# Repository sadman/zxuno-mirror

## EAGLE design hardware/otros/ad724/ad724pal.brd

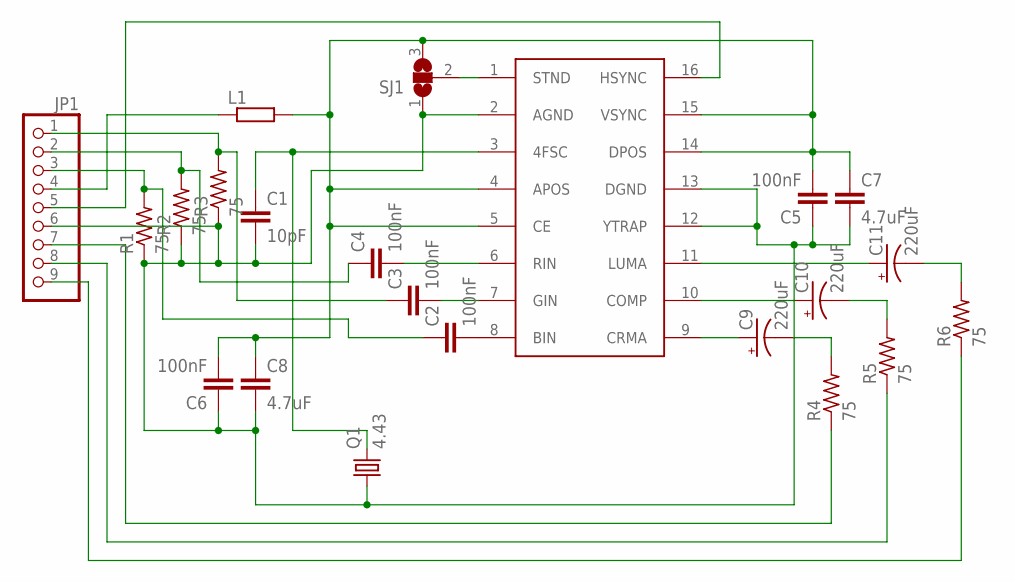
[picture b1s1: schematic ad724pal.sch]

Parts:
C1: 10pF; C0805
C2, C3, C4, C5, C6: 100nF; C0603
C7, C8: 4.7uF; C0805
C9, C10, C11: 220uF; E2,5-6
JP1: PINHD-1X9; 1X09
L1: R-EU_R0805; R0805
Q1: 4.43; HC49/S
R1, R2, R3, R4, R5, R6: 75; R0805
SJ1: SJ2W; SJ_2
U1: AD725; SO16W

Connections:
GND: C1.2, C5.1, C6.1, C7.2, C8.2, JP1.6, Q1.1, R1.1, R2.1, R3.1, SJ1.1, U1.2 (AGND), U1.12 (YTRAP), U1.13 (DGND)
unnamed: C4.1, JP1.2, R2.2
unnamed: SJ1.2, U1.1 (STND)
unnamed: C5.2, C6.2, C7.1, C8.1, L1.2, SJ1.3, U1.4 (APOS), U1.5 (CE), U1.14 (DPOS), U1.15 (VSYNC)
unnamed: C4.2, U1.6 (RIN)
unnamed: JP1.4, L1.1
unnamed: JP1.5, U1.16 (HSYNC)
unnamed: C3.2, U1.7 (GIN)
unnamed: C2.2, U1.8 (BIN)
unnamed: C3.1, JP1.1, R3.2
unnamed: C2.1, JP1.3, R1.2
unnamed: C1.1, Q1.2, U1.3 (4FSC)
unnamed: C11.+, U1.11 (LUMA)
unnamed: C10.+, U1.10 (COMP)
unnamed: C9.+, U1.9 (CRMA)
unnamed: C11.-, R6.2
unnamed: C10.-, R5.2
unnamed: C9.-, R4.2
unnamed: JP1.7, R4.1
unnamed: JP1.8, R5.1
unnamed: JP1.9, R6.1

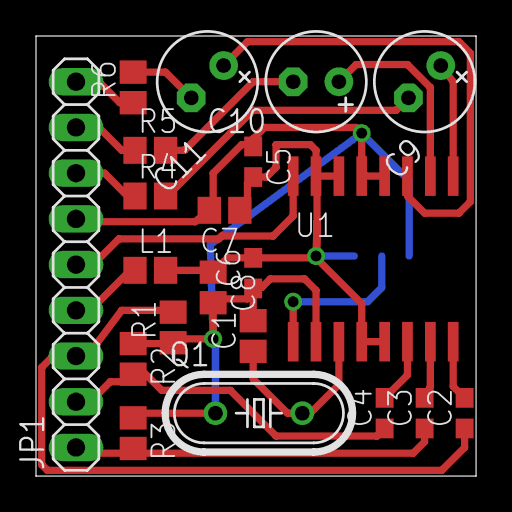
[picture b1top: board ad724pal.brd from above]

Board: 2 copper layers, 24.4 x 24.4 mm, 22 parts (1 on the bottom side), 21 nets.

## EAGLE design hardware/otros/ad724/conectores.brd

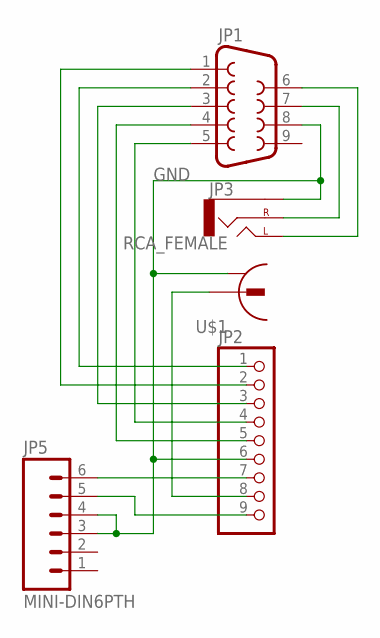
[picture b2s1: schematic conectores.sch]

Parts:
JP1: DB9MALE; DB9_MALE
JP2: PINHD-1X9; 1X09
JP3: AUDIO-JACKPTH; AUDIO-JACK
JP5: MINI-DIN6PTH; MINI-DIN6
U$1: RCA_FEMALE; RCA_EBAY

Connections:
GND: JP1.8, JP2.6, JP3.SLEEVE, JP5.3, JP5.4, U$1.1 (2)
unnamed: JP1.1, JP2.2
unnamed: JP1.2, JP2.1
unnamed: JP1.3, JP2.3
unnamed: JP1.4, JP2.5
unnamed: JP1.5, JP2.4
unnamed: JP1.6, JP3.TIP (LEFT)
unnamed: JP1.7, JP3.RING (RIGHT)
unnamed: JP2.9, JP5.5
unnamed: JP2.8, U$1.2 (1)
unnamed: JP2.7, JP5.6

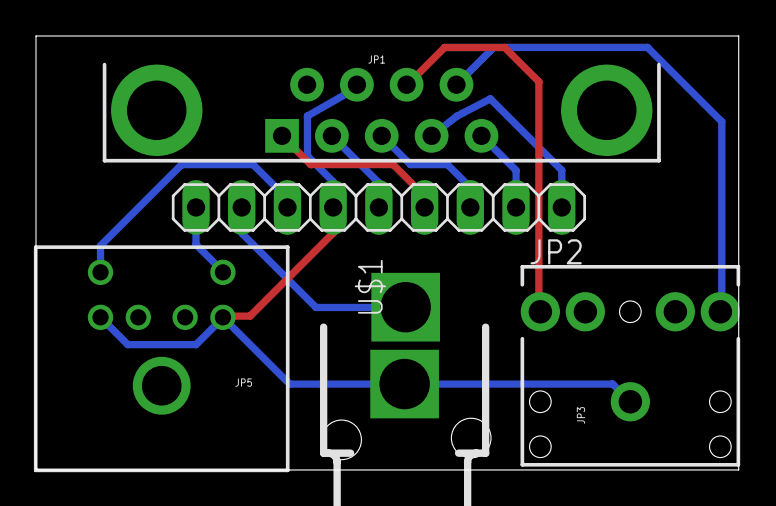
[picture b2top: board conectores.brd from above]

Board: 2 copper layers, 39.0 x 24.1 mm, 5 parts (0 on the bottom side), 11 nets.

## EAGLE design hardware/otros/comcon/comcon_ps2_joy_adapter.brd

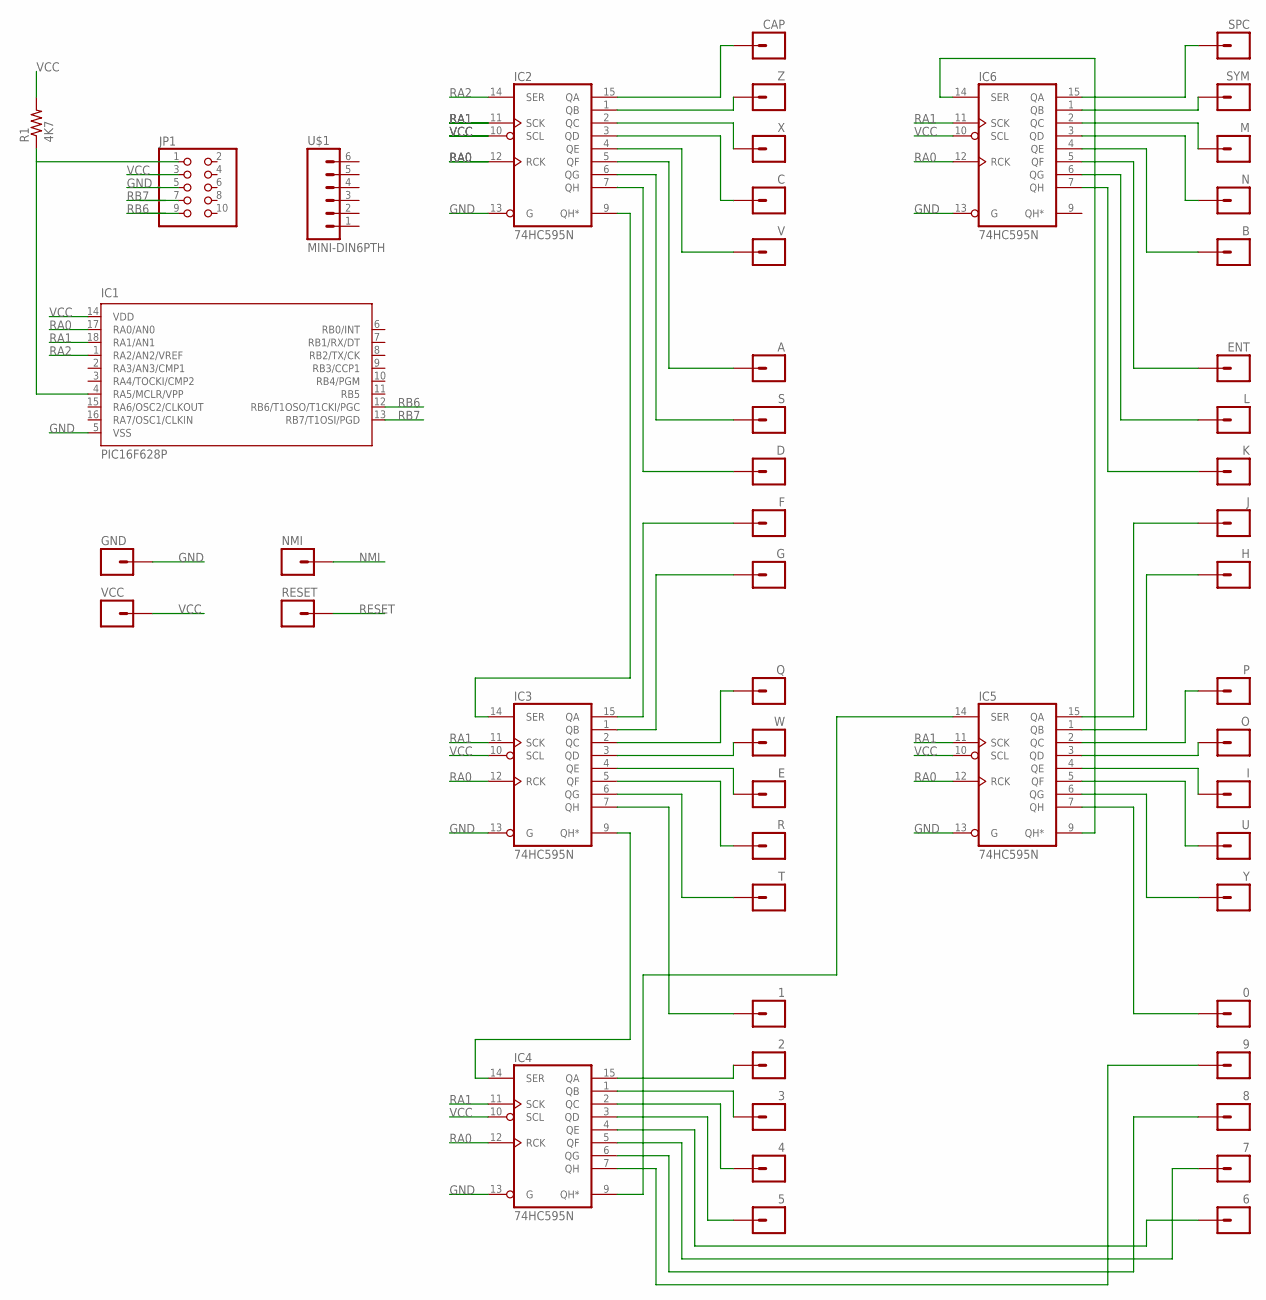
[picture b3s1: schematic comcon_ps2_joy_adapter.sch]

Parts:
0, 1, 2, 3, 4, 5, 6, 7, 8, 9: M01PTH; 1X01
A: M01PTH; 1X01
B: M01PTH; 1X01
C: M01PTH; 1X01
CAP: M01PTH; 1X01
D: M01PTH; 1X01
E: M01PTH; 1X01
ENT: M01PTH; 1X01
F: M01PTH; 1X01
G: M01PTH; 1X01
GND: M01PTH; 1X01
H: M01PTH; 1X01
I: M01PTH; 1X01
IC1: PIC16F628P; DIL18
IC2, IC3, IC4, IC5, IC6: 74HC595N; DIL16
J: M01PTH; 1X01
JP1: PINHD-2X5; 2X05
K: M01PTH; 1X01
L: M01PTH; 1X01
M: M01PTH; 1X01
N: M01PTH; 1X01
NMI: M01PTH; 1X01
O: M01PTH; 1X01
P: M01PTH; 1X01
Q: M01PTH; 1X01
R: M01PTH; 1X01
R1: 4K7; 0207/7
RESET: M01PTH; 1X01
S: M01PTH; 1X01
SPC: M01PTH; 1X01
SYM: M01PTH; 1X01
T: M01PTH; 1X01
U: M01PTH; 1X01
U$1: MINI-DIN6PTH; MINI-DIN6
V: M01PTH; 1X01
VCC: M01PTH; 1X01
W: M01PTH; 1X01
X: M01PTH; 1X01
Y: M01PTH; 1X01
Z: M01PTH; 1X01

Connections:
GND: GND.1, IC1.5 (VSS), IC2.8 (GND), IC2.13 (G), IC3.8 (GND), IC3.13 (G), IC4.8 (GND), IC4.13 (G), IC5.8 (GND), IC5.13 (G), IC6.8 (GND), IC6.13 (G), JP1.5
unnamed: A.1, IC2.5 (QF)
unnamed: IC2.6 (QG), S.1
unnamed: IC2.9 (QH*), IC3.14 (SER)
unnamed: IC5.9 (QH*), IC6.14 (SER)
unnamed: IC3.9 (QH*), IC4.14 (SER)
unnamed: IC4.9 (QH*), IC5.14 (SER)
unnamed: IC1.4 (RA5/MCLR/VPP), JP1.1, R1.1
unnamed: IC6.1 (QB), SYM.1
unnamed: IC6.2 (QC), M.1
unnamed: IC6.3 (QD), N.1
unnamed: B.1, IC6.4 (QE)
unnamed: CAP.1, IC2.15 (QA)
unnamed: IC2.1 (QB), Z.1
unnamed: IC2.2 (QC), X.1
unnamed: C.1, IC2.3 (QD)
unnamed: IC2.4 (QE), V.1
unnamed: ENT.1, IC6.5 (QF)
unnamed: IC6.6 (QG), L.1
unnamed: IC6.7 (QH), K.1
unnamed: IC5.15 (QA), J.1
unnamed: H.1, IC5.1 (QB)
unnamed: D.1, IC2.7 (QH)
unnamed: F.1, IC3.15 (QA)
unnamed: G.1, IC3.1 (QB)
unnamed: IC5.3 (QD), O.1
unnamed: I.1, IC5.4 (QE)
unnamed: IC5.5 (QF), U.1
unnamed: IC5.6 (QG), Y.1
unnamed: IC3.3 (QD), W.1
unnamed: E.1, IC3.4 (QE)
unnamed: IC3.5 (QF), R.1
unnamed: IC3.6 (QG), T.1
unnamed: 0.1, IC5.7 (QH)
unnamed: 9.1, IC4.7 (QH)
unnamed: 8.1, IC4.6 (QG)
unnamed: 7.1, IC4.5 (QF)
unnamed: 6.1, IC4.4 (QE)
unnamed: 1.1, IC3.7 (QH)
unnamed: 2.1, IC4.15 (QA)
unnamed: 3.1, IC4.1 (QB)
unnamed: 4.1, IC4.2 (QC)
unnamed: 5.1, IC4.3 (QD)
NMI: NMI.1
RA0: IC2.12 (RCK), IC3.12 (RCK), IC4.12 (RCK), IC5.12 (RCK), IC6.12 (RCK)
RA1: IC2.11 (SCK), IC3.11 (SCK), IC4.11 (SCK), IC5.11 (SCK), IC6.11 (SCK)
RA2: IC2.14 (SER)
RB6: IC1.12 (RB6/T1OSO/T1CKI/PGC)
RB7: IC1.13 (RB7/T1OSI/PGD)
RESET: RESET.1
VCC: IC2.10 (SCL), IC2.16 (VCC), IC3.10 (SCL), IC3.16 (VCC), IC4.10 (SCL), IC4.16 (VCC), IC5.10 (SCL), IC5.16 (VCC), IC6.10 (SCL), IC6.16 (VCC), JP1.3, R1.2, VCC.1
VDD: IC1.14 (VDD)

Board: 2 copper layers, 53 parts (0 on the bottom side), 46 nets, no tracks yet.

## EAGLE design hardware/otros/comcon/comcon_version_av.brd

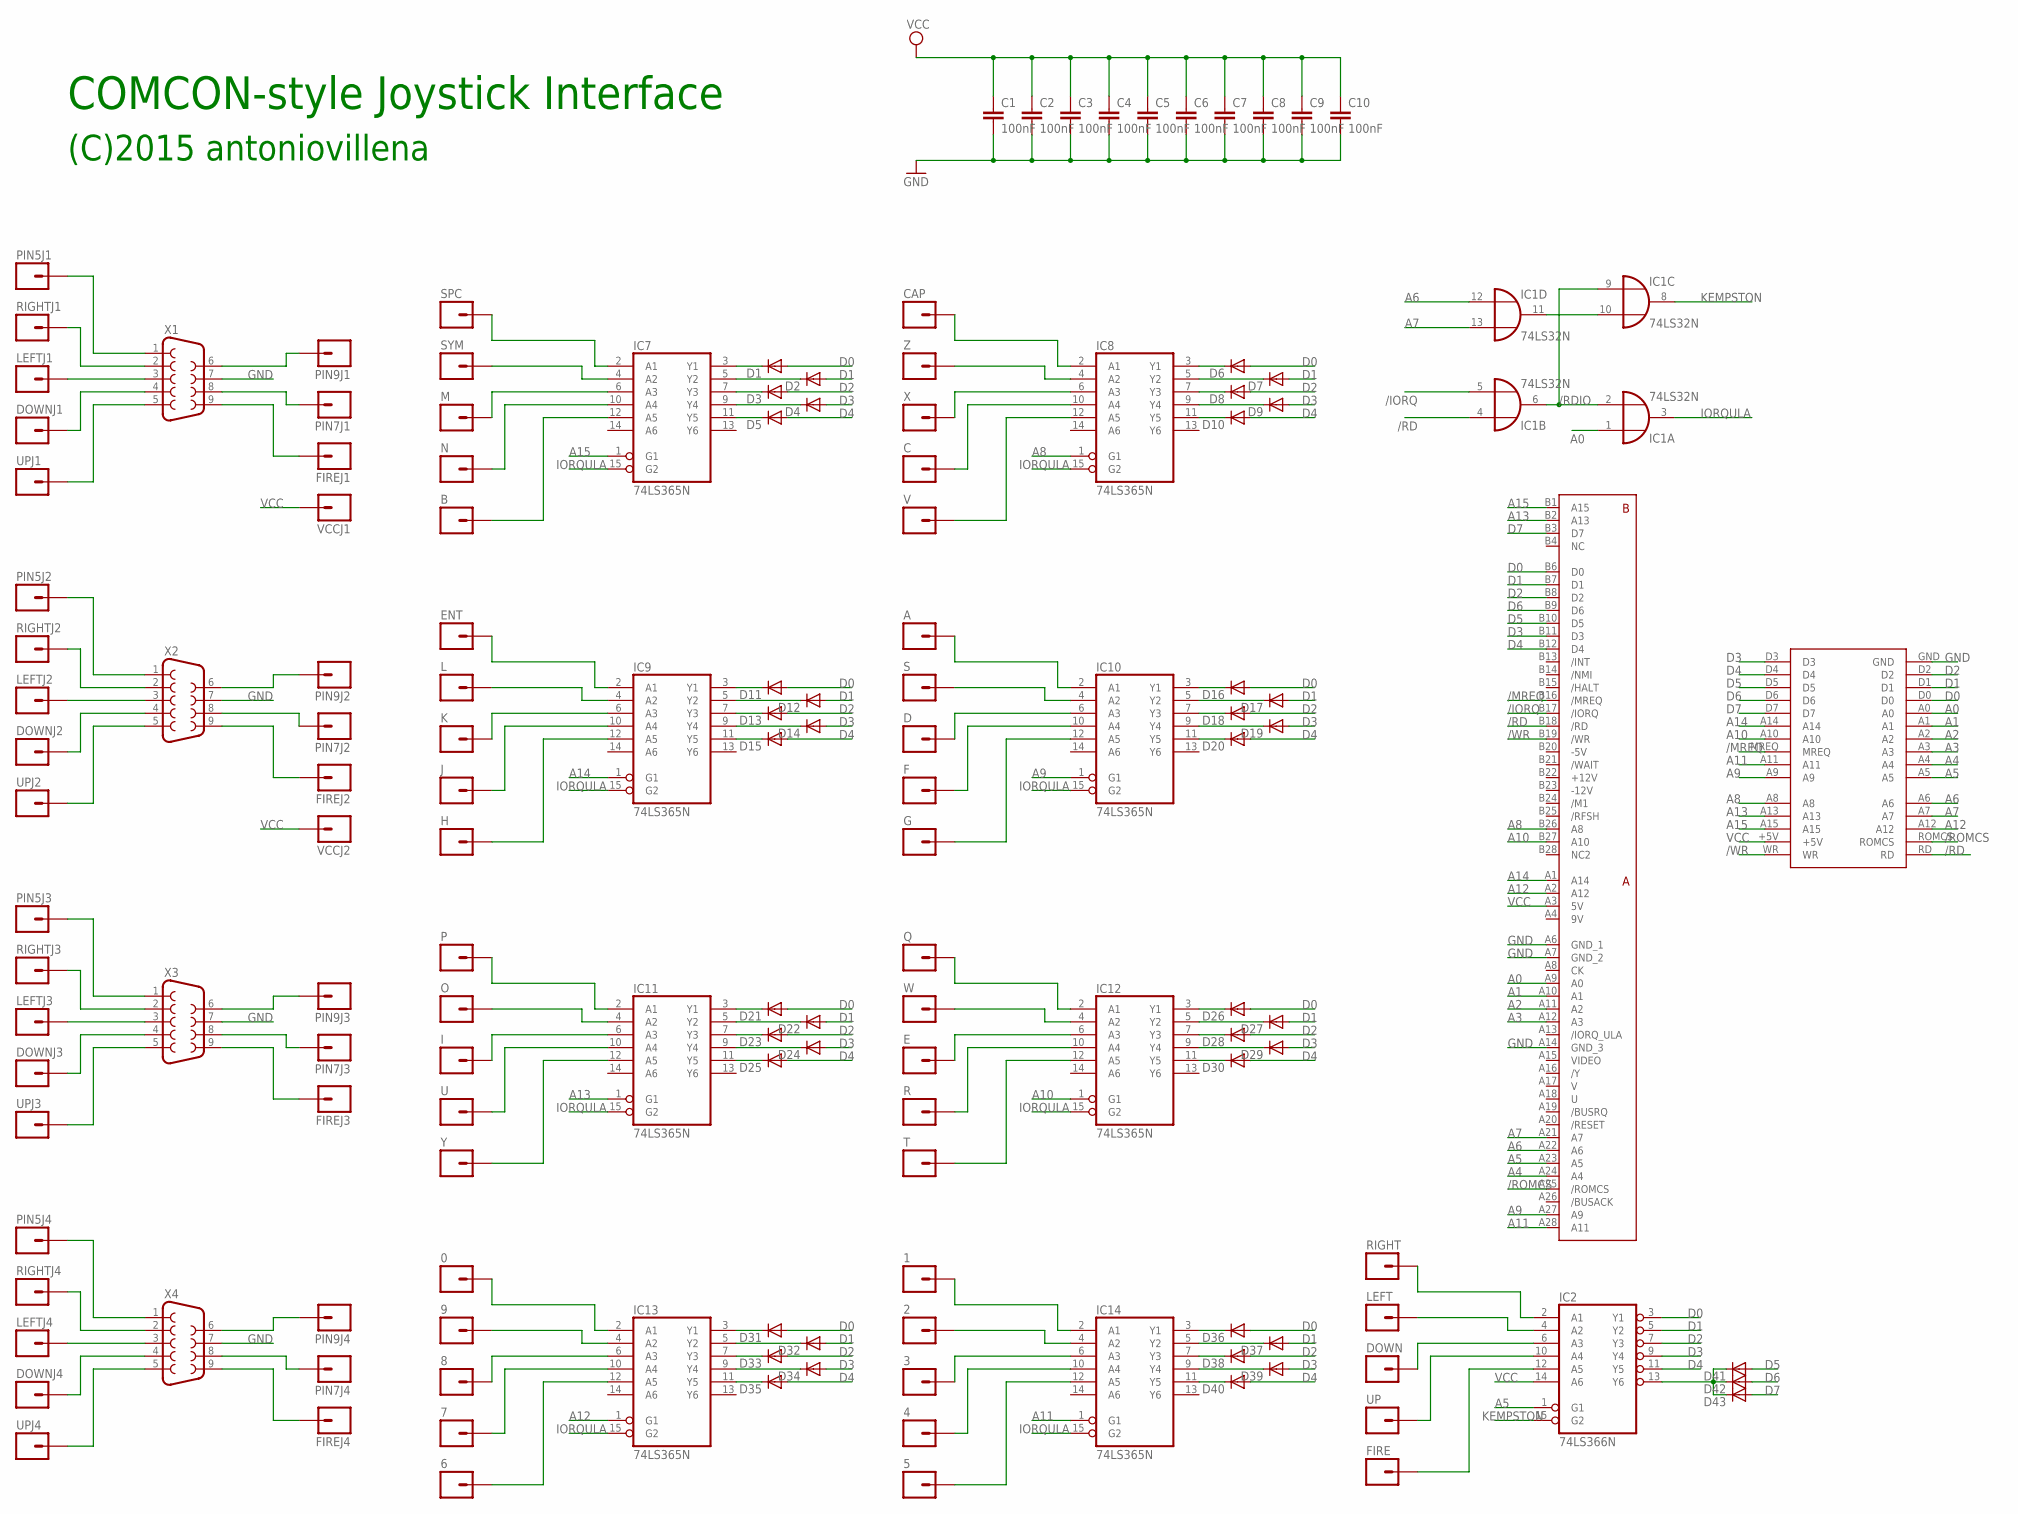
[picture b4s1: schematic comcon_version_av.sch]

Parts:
0, 1, 2, 3, 4, 5, 6, 7, 8, 9: M01PTH; 1X01
A: M01PTH; 1X01
B: M01PTH; 1X01
C: M01PTH; 1X01
C1, C2, C3, C4, C5, C6, C7, C8, C9, C10: 100nF; C050-025X075
CAP: M01PTH; 1X01
D: M01PTH; 1X01
D1, D2, D3, D4, D5, D6, D7, D8, D9, D10, D11, D12, D13, D14, D15, D16, D17, D18, D19, D20, D21, D22, D23, D24, D25, D26, D27, D28, D29, D30, D31, D32, D33, D34, D35, D36, D37, D38, D39, D40, D43: 1N4148DO35-7; DO35-7
D41, D42: 1N4148DO35-10; DO35-10
DOWN: M01PTH; 1X01
DOWNJ1, DOWNJ2, DOWNJ3, DOWNJ4: M01PTH; 1X01
E: M01PTH; 1X01
ENT: M01PTH; 1X01
F: M01PTH; 1X01
FIRE: M01PTH; 1X01
FIREJ1, FIREJ2, FIREJ3, FIREJ4: M01PTH; 1X01
G: M01PTH; 1X01
H: M01PTH; 1X01
I: M01PTH; 1X01
IC1: 74LS32N; DIL14
IC2: 74LS366N; DIL16
IC7, IC8, IC9, IC10, IC11, IC12, IC13, IC14: 74LS365N; DIL16
J: M01PTH; 1X01
K: M01PTH; 1X01
L: M01PTH; 1X01
LEFT: M01PTH; 1X01
LEFTJ1, LEFTJ2, LEFTJ3, LEFTJ4: M01PTH; 1X01
M: M01PTH; 1X01
N: M01PTH; 1X01
O: M01PTH; 1X01
P: M01PTH; 1X01
PIN5J1, PIN5J2, PIN5J3, PIN5J4, PIN7J1, PIN7J2, PIN7J3, PIN7J4, PIN9J1, PIN9J2, PIN9J3, PIN9J4: M01PTH; 1X01
Q: M01PTH; 1X01
R: M01PTH; 1X01
RIGHT: M01PTH; 1X01
RIGHTJ1, RIGHTJ2, RIGHTJ3, RIGHTJ4: M01PTH; 1X01
S: M01PTH; 1X01
SPC: M01PTH; 1X01
SYM: M01PTH; 1X01
T: M01PTH; 1X01
U: M01PTH; 1X01
U$1: ZX_CARTRIDGE
U$3: ZXSP_ED2X28_SPE; 2X28_SPE
UP: M01PTH; 1X01
UPJ1, UPJ2, UPJ3, UPJ4: M01PTH; 1X01
V: M01PTH; 1X01
VCCJ1, VCCJ2: M01PTH; 1X01
W: M01PTH; 1X01
X: M01PTH; 1X01
X1, X2, X3, X4: F09D
Y: M01PTH; 1X01
Z: M01PTH; 1X01

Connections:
9V: U$3.A4 (9V)
+12V: U$3.B22 (+12V)
-5V: U$3.B20 (-5V)
-12V: U$3.B23 (-12V)
/IORQ: IC1.5 (I1), U$3.B17 (/IORQ)
/MREQ: U$1.MREQ, U$3.B16 (/MREQ)
/RD: IC1.4 (I0), U$1.RD, U$3.B18 (/RD)
/RDIO: IC1.2 (I1), IC1.6 (O), IC1.9 (I0)
/ROMCS: U$1.ROMCS, U$3.A25 (/ROMCS)
/WR: U$1.WR, U$3.B19 (/WR)
A0: IC1.1 (I0), U$1.A0, U$3.A9 (A0)
A1: U$1.A1, U$3.A10 (A1)
A2: U$1.A2, U$3.A11 (A2)
A3: U$1.A3, U$3.A12 (A3)
A4: U$1.A4, U$3.A24 (A4)
A5: IC2.1 (G1), U$1.A5, U$3.A23 (A5)
A6: IC1.12 (I0), U$1.A6, U$3.A22 (A6)
A7: IC1.13 (I1), U$1.A7, U$3.A21 (A7)
A8: IC8.1 (G1), U$1.A8, U$3.B26 (A8)
A9: IC10.1 (G1), U$1.A9, U$3.A27 (A9)
A10: IC12.1 (G1), U$1.A10, U$3.B27 (A10)
A11: IC14.1 (G1), U$1.A11, U$3.A28 (A11)
A12: IC13.1 (G1), U$1.A12, U$3.A2 (A12)
A13: IC11.1 (G1), U$1.A13, U$3.B2 (A13)
A14: IC9.1 (G1), U$1.A14, U$3.A1 (A14)
A15: IC7.1 (G1), U$1.A15, U$3.B1 (A15)
D0: D1.A, D6.A, D11.A, D16.A, D21.A, D26.A, D31.A, D36.A, IC2.3 (Y1), U$1.D0, U$3.B6 (D0)
D1: D2.A, D7.A, D12.A, D17.A, D22.A, D27.A, D32.A, D37.A, IC2.5 (Y2), U$1.D1, U$3.B7 (D1)
D2: D3.A, D8.A, D13.A, D18.A, D23.A, D28.A, D33.A, D38.A, IC2.7 (Y3), U$1.D2, U$3.B8 (D2)
D3: D4.A, D9.A, D14.A, D19.A, D24.A, D29.A, D34.A, D39.A, IC2.9 (Y4), U$1.D3, U$3.B11 (D3)
D4: D5.A, D10.A, D15.A, D20.A, D25.A, D30.A, D35.A, D40.A, IC2.11 (Y5), U$1.D4, U$3.B12 (D4)
D5: D41.A, U$1.D5, U$3.B10 (D5)
D6: D42.A, U$1.D6, U$3.B9 (D6)
D7: D43.A, U$1.D7, U$3.B3 (D7)
GND: C1.2, C2.2, C3.2, C4.2, C5.2, C6.2, C7.2, C8.2, C9.2, C10.2, IC1.7 (GND), IC2.8 (GND), IC7.8 (GND), IC8.8 (GND), IC9.8 (GND), IC10.8 (GND), IC11.8 (GND), IC12.8 (GND), IC13.8 (GND), IC14.8 (GND), U$1.GND, U$3.A6 (GND_1), U$3.A7 (GND_2), U$3.A14 (GND_3), X1.7, X2.7, X3.7, X4.7
IORQULA: IC1.3 (O), IC7.15 (G2), IC8.15 (G2), IC9.15 (G2), IC10.15 (G2), IC11.15 (G2), IC12.15 (G2), IC13.15 (G2), IC14.15 (G2)
KEMPSTON: IC1.8 (O), IC2.15 (G2)
unnamed: D41.C, D42.C, D43.C, IC2.13 (Y6)
unnamed: IC7.2 (A1), SPC.1
unnamed: D1.C, IC7.3 (Y1)
unnamed: IC1.10 (I1), IC1.11 (O)
unnamed: PIN5J1.1, X1.1
unnamed: RIGHTJ1.1, X1.2
unnamed: LEFTJ1.1, X1.3
unnamed: DOWNJ1.1, X1.4
unnamed: UPJ1.1, X1.5
unnamed: PIN9J1.1, X1.6
unnamed: FIREJ1.1, X1.9
unnamed: IC7.4 (A2), SYM.1
unnamed: PIN5J2.1, X2.1
unnamed: RIGHTJ2.1, X2.2
unnamed: LEFTJ2.1, X2.3
unnamed: DOWNJ2.1, X2.4
unnamed: UPJ2.1, X2.5
unnamed: IC7.6 (A3), M.1
unnamed: D2.C, IC7.5 (Y2)
unnamed: IC7.10 (A4), N.1
unnamed: D3.C, IC7.7 (Y3)
unnamed: B.1, IC7.12 (A5)
unnamed: D4.C, IC7.9 (Y4)
unnamed: D5.C, IC7.11 (Y5)
unnamed: CAP.1, IC8.2 (A1)
unnamed: IC8.4 (A2), Z.1
unnamed: IC8.6 (A3), X.1
unnamed: C.1, IC8.10 (A4)
unnamed: PIN9J2.1, X2.6
unnamed: FIREJ2.1, X2.9
unnamed: PIN7J1.1, X1.8
unnamed: PIN7J2.1, X2.8
unnamed: PIN5J3.1, X3.1
unnamed: RIGHTJ3.1, X3.2
unnamed: LEFTJ3.1, X3.3
unnamed: IC2.2 (A1), RIGHT.1
unnamed: IC2.4 (A2), LEFT.1
unnamed: DOWN.1, IC2.6 (A3)
unnamed: IC2.10 (A4), UP.1
unnamed: FIRE.1, IC2.12 (A5)
unnamed: DOWNJ3.1, X3.4
unnamed: UPJ3.1, X3.5
unnamed: PIN9J3.1, X3.6
unnamed: FIREJ3.1, X3.9
unnamed: PIN7J3.1, X3.8
unnamed: PIN5J4.1, X4.1
unnamed: IC8.12 (A5), V.1
unnamed: D6.C, IC8.3 (Y1)
unnamed: D7.C, IC8.5 (Y2)
unnamed: D8.C, IC8.7 (Y3)
unnamed: D9.C, IC8.9 (Y4)
unnamed: D10.C, IC8.11 (Y5)
unnamed: ENT.1, IC9.2 (A1)
unnamed: IC9.4 (A2), L.1
unnamed: IC9.6 (A3), K.1
unnamed: IC9.10 (A4), J.1
unnamed: H.1, IC9.12 (A5)
unnamed: D11.C, IC9.3 (Y1)
unnamed: D12.C, IC9.5 (Y2)
unnamed: D13.C, IC9.7 (Y3)
unnamed: D14.C, IC9.9 (Y4)
unnamed: D15.C, IC9.11 (Y5)
unnamed: A.1, IC10.2 (A1)
unnamed: IC10.4 (A2), S.1
unnamed: D.1, IC10.6 (A3)
unnamed: F.1, IC10.10 (A4)
unnamed: G.1, IC10.12 (A5)
unnamed: D16.C, IC10.3 (Y1)
unnamed: D17.C, IC10.5 (Y2)
unnamed: D18.C, IC10.7 (Y3)
unnamed: D19.C, IC10.9 (Y4)
unnamed: D20.C, IC10.11 (Y5)
unnamed: RIGHTJ4.1, X4.2
unnamed: IC11.2 (A1), P.1
unnamed: IC11.4 (A2), O.1
unnamed: I.1, IC11.6 (A3)
unnamed: IC11.10 (A4), U.1
unnamed: IC11.12 (A5), Y.1
unnamed: D21.C, IC11.3 (Y1)
unnamed: D22.C, IC11.5 (Y2)
unnamed: D23.C, IC11.7 (Y3)
unnamed: D24.C, IC11.9 (Y4)
unnamed: D25.C, IC11.11 (Y5)
unnamed: IC12.2 (A1), Q.1
unnamed: IC12.4 (A2), W.1
unnamed: E.1, IC12.6 (A3)
unnamed: IC12.10 (A4), R.1
unnamed: IC12.12 (A5), T.1
unnamed: D26.C, IC12.3 (Y1)
unnamed: D27.C, IC12.5 (Y2)
unnamed: D28.C, IC12.7 (Y3)
unnamed: D29.C, IC12.9 (Y4)
unnamed: D30.C, IC12.11 (Y5)
unnamed: 0.1, IC13.2 (A1)
unnamed: 9.1, IC13.4 (A2)
unnamed: 8.1, IC13.6 (A3)
unnamed: 7.1, IC13.10 (A4)
unnamed: 6.1, IC13.12 (A5)
unnamed: D31.C, IC13.3 (Y1)
unnamed: D32.C, IC13.5 (Y2)
unnamed: D33.C, IC13.7 (Y3)
unnamed: D34.C, IC13.9 (Y4)
unnamed: D35.C, IC13.11 (Y5)
unnamed: 1.1, IC14.2 (A1)
unnamed: 2.1, IC14.4 (A2)
unnamed: 3.1, IC14.6 (A3)
unnamed: 4.1, IC14.10 (A4)
unnamed: 5.1, IC14.12 (A5)
unnamed: D36.C, IC14.3 (Y1)
unnamed: D37.C, IC14.5 (Y2)
unnamed: D38.C, IC14.7 (Y3)
unnamed: D39.C, IC14.9 (Y4)
unnamed: D40.C, IC14.11 (Y5)
unnamed: LEFTJ4.1, X4.3
unnamed: DOWNJ4.1, X4.4
unnamed: UPJ4.1, X4.5
unnamed: PIN9J4.1, X4.6
unnamed: FIREJ4.1, X4.9
unnamed: PIN7J4.1, X4.8
VCC: C1.1, C2.1, C3.1, C4.1, C5.1, C6.1, C7.1, C8.1, C9.1, C10.1, IC1.14 (VCC), IC2.14 (A6), IC2.16 (VCC), IC7.16 (VCC), IC8.16 (VCC), IC9.16 (VCC), IC10.16 (VCC), IC11.16 (VCC), IC12.16 (VCC), IC13.16 (VCC), IC14.16 (VCC), U$1.+5V, U$3.A3 (5V), VCCJ1.1, VCCJ2.1

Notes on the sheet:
COMCON-style Joystick Interface
(C)2015 antoniovillena

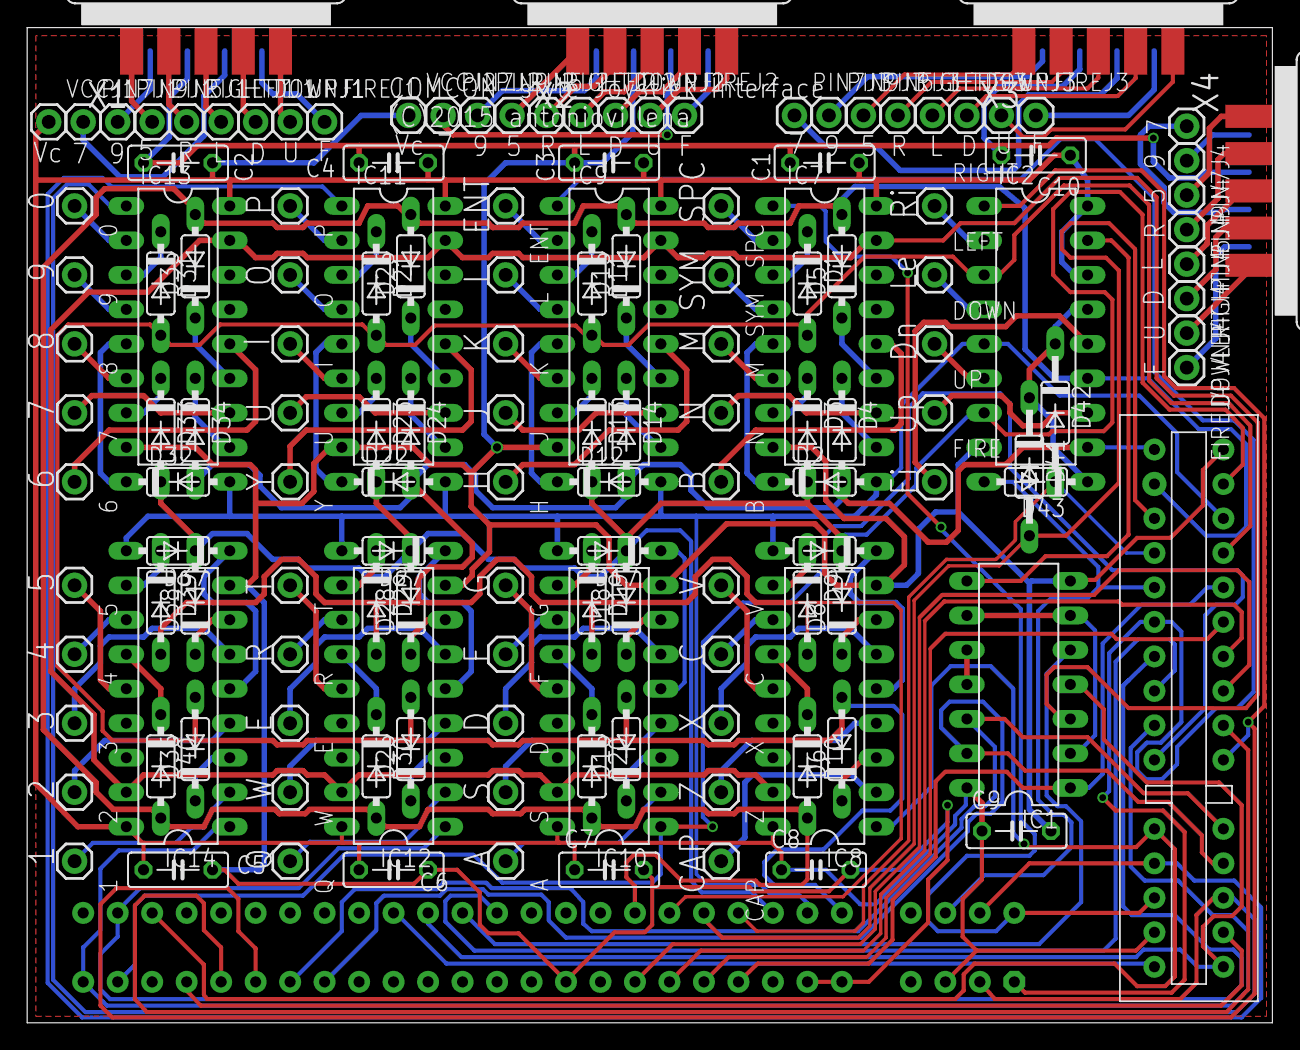
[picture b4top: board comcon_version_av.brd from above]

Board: 2 copper layers, 91.7 x 73.3 mm, 148 parts (1 on the bottom side), 153 nets.

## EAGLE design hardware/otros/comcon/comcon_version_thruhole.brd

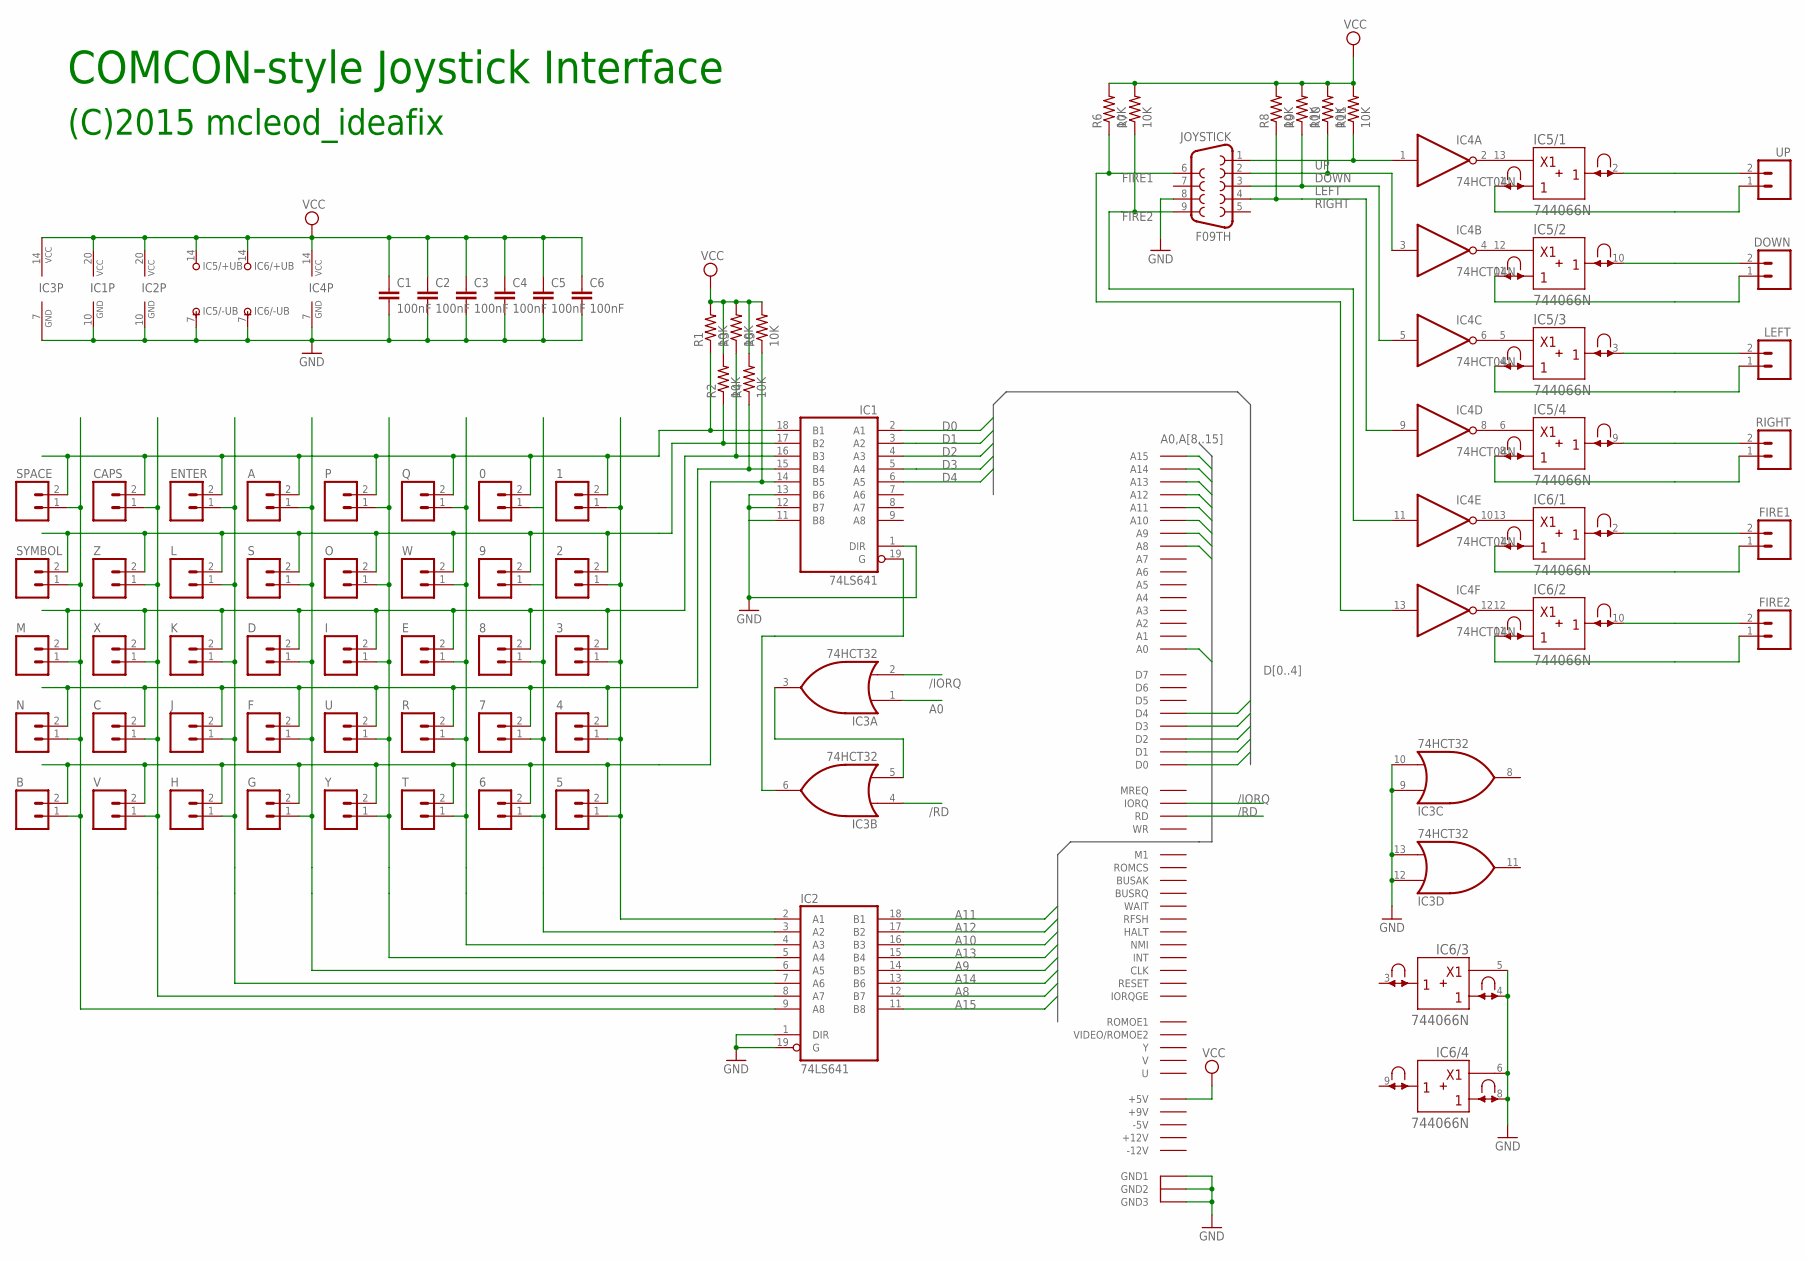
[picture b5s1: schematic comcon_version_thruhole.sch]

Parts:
0, 1, 2, 3, 4, 5, 6, 7, 8, 9: M02PTH; 1X02
A: M02PTH; 1X02
B: M02PTH; 1X02
C: M02PTH; 1X02
C1, C2, C3, C4, C5, C6: 100nF; C050-025X075
CAPS: M02PTH; 1X02
D: M02PTH; 1X02
DOWN: M02PTH; 1X02
E: M02PTH; 1X02
ENTER: M02PTH; 1X02
F: M02PTH; 1X02
FIRE1, FIRE2: M02PTH; 1X02
G: M02PTH; 1X02
H: M02PTH; 1X02
I: M02PTH; 1X02
IC1, IC2: 74LS641; DIL20
IC3: 74HCT32; DIL14
IC4: 74HCT04N; DIL14
IC5, IC6: 744066N; DIL14
J: M02PTH; 1X02
JOYSTICK: F09TH; DB9_PCB
K: M02PTH; 1X02
L: M02PTH; 1X02
LEFT: M02PTH; 1X02
M: M02PTH; 1X02
N: M02PTH; 1X02
O: M02PTH; 1X02
P: M02PTH; 1X02
Q: M02PTH; 1X02
R: M02PTH; 1X02
R1, R2, R3, R4, R5, R6, R7, R8, R9, R10, R11: 10K; 0207/10
RIGHT: M02PTH; 1X02
S: M02PTH; 1X02
SPACE: M02PTH; 1X02
SYMBOL: M02PTH; 1X02
T: M02PTH; 1X02
U: M02PTH; 1X02
UP: M02PTH; 1X02
V: M02PTH; 1X02
W: M02PTH; 1X02
X: M02PTH; 1X02
Y: M02PTH; 1X02
Z: M02PTH; 1X02
ZX_BUS: CONECTOR_SPECTRUM

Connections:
/IORQ: IC3.2 (I1), ZX_BUS.IORQ
/RD: IC3.4 (I0), ZX_BUS.RD
A0: IC3.1 (I0), ZX_BUS.A0
A8: IC2.12 (B7), ZX_BUS.A8
A9: IC2.14 (B5), ZX_BUS.A9
A10: IC2.16 (B3), ZX_BUS.A10
A11: IC2.18 (B1), ZX_BUS.A11
A12: IC2.17 (B2), ZX_BUS.A12
A13: IC2.15 (B4), ZX_BUS.A13
A14: IC2.13 (B6), ZX_BUS.A14
A15: IC2.11 (B8), ZX_BUS.A15
D0: IC1.2 (A1), ZX_BUS.D0
D1: IC1.3 (A2), ZX_BUS.D1
D2: IC1.4 (A3), ZX_BUS.D2
D3: IC1.5 (A4), ZX_BUS.D3
D4: IC1.6 (A5), ZX_BUS.D4
DOWN: IC4.3 (I), JOYSTICK.2, R10.1
FIRE1: IC4.13 (I), JOYSTICK.6, R6.1
FIRE2: IC4.11 (I), JOYSTICK.9, R7.1
GND: C1.2, C2.2, C3.2, C4.2, C5.2, C6.2, IC1.1 (DIR), IC1.10 (GND), IC1.11 (B8), IC1.12 (B7), IC1.13 (B6), IC2.1 (DIR), IC2.10 (GND), IC2.19 (G), IC3.7 (GND), IC3.9 (I0), IC3.10 (I1), IC3.12 (I0), IC3.13 (I1), IC4.7 (GND), IC5.7 (-UB), IC6.4 (A), IC6.5 (C), IC6.6 (C), IC6.7 (-UB), IC6.8 (A), JOYSTICK.8, ZX_BUS.GND1, ZX_BUS.GND2, ZX_BUS.GND3
LEFT: IC4.5 (I), JOYSTICK.3, R9.1
unnamed: IC3.3 (O), IC3.5 (I1)
unnamed: IC1.19 (G), IC3.6 (O)
unnamed: 1.1, 2.1, 3.1, 4.1, 5.1, IC2.2 (A1)
unnamed: 0.1, 6.1, 7.1, 8.1, 9.1, IC2.3 (A2)
unnamed: E.1, IC2.4 (A3), Q.1, R.1, T.1, W.1
unnamed: I.1, IC2.5 (A4), O.1, P.1, U.1, Y.1
unnamed: A.1, D.1, F.1, G.1, IC2.6 (A5), S.1
unnamed: ENTER.1, H.1, IC2.7 (A6), J.1, K.1, L.1
unnamed: C.1, CAPS.1, IC2.8 (A7), V.1, X.1, Z.1
unnamed: B.1, IC2.9 (A8), M.1, N.1, SPACE.1, SYMBOL.1
unnamed: 0.2, 1.2, A.2, CAPS.2, ENTER.2, IC1.18 (B1), P.2, Q.2, R1.1, SPACE.2
unnamed: 2.2, 9.2, IC1.17 (B2), L.2, O.2, R2.1, S.2, SYMBOL.2, W.2, Z.2
unnamed: 3.2, 8.2, D.2, E.2, I.2, IC1.16 (B3), K.2, M.2, R3.1, X.2
unnamed: 4.2, 7.2, C.2, F.2, IC1.15 (B4), J.2, N.2, R.2, R4.1, U.2
unnamed: 5.2, 6.2, B.2, G.2, H.2, IC1.14 (B5), R5.1, T.2, V.2, Y.2
unnamed: DOWN.1, IC5.11 (A)
unnamed: IC5.4 (A), LEFT.1
unnamed: IC5.8 (A), RIGHT.1
unnamed: FIRE1.1, IC6.1 (A)
unnamed: IC4.2 (O), IC5.13 (C)
unnamed: IC4.4 (O), IC5.12 (C)
unnamed: IC4.6 (O), IC5.5 (C)
unnamed: IC4.8 (O), IC5.6 (C)
unnamed: IC4.10 (O), IC6.13 (C)
unnamed: IC4.12 (O), IC6.12 (C)
unnamed: IC5.1 (A), UP.1
unnamed: FIRE2.1, IC6.11 (A)
unnamed: IC5.2 (B), UP.2
unnamed: DOWN.2, IC5.10 (B)
unnamed: IC5.3 (B), LEFT.2
unnamed: IC5.9 (B), RIGHT.2
unnamed: FIRE1.2, IC6.2 (B)
unnamed: FIRE2.2, IC6.10 (B)
RIGHT: IC4.9 (I), JOYSTICK.4, R8.1
UP: IC4.1 (I), JOYSTICK.1, R11.1
VCC: C1.1, C2.1, C3.1, C4.1, C5.1, C6.1, IC1.20 (VCC), IC2.20 (VCC), IC3.14 (VCC), IC4.14 (VCC), IC5.14 (+UB), IC6.14 (+UB), R1.2, R2.2, R3.2, R4.2, R5.2, R6.2, R7.2, R8.2, R9.2, R10.2, R11.2, ZX_BUS.+5V

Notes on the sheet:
COMCON-style Joystick Interface
(C)2015 mcleod_ideafix

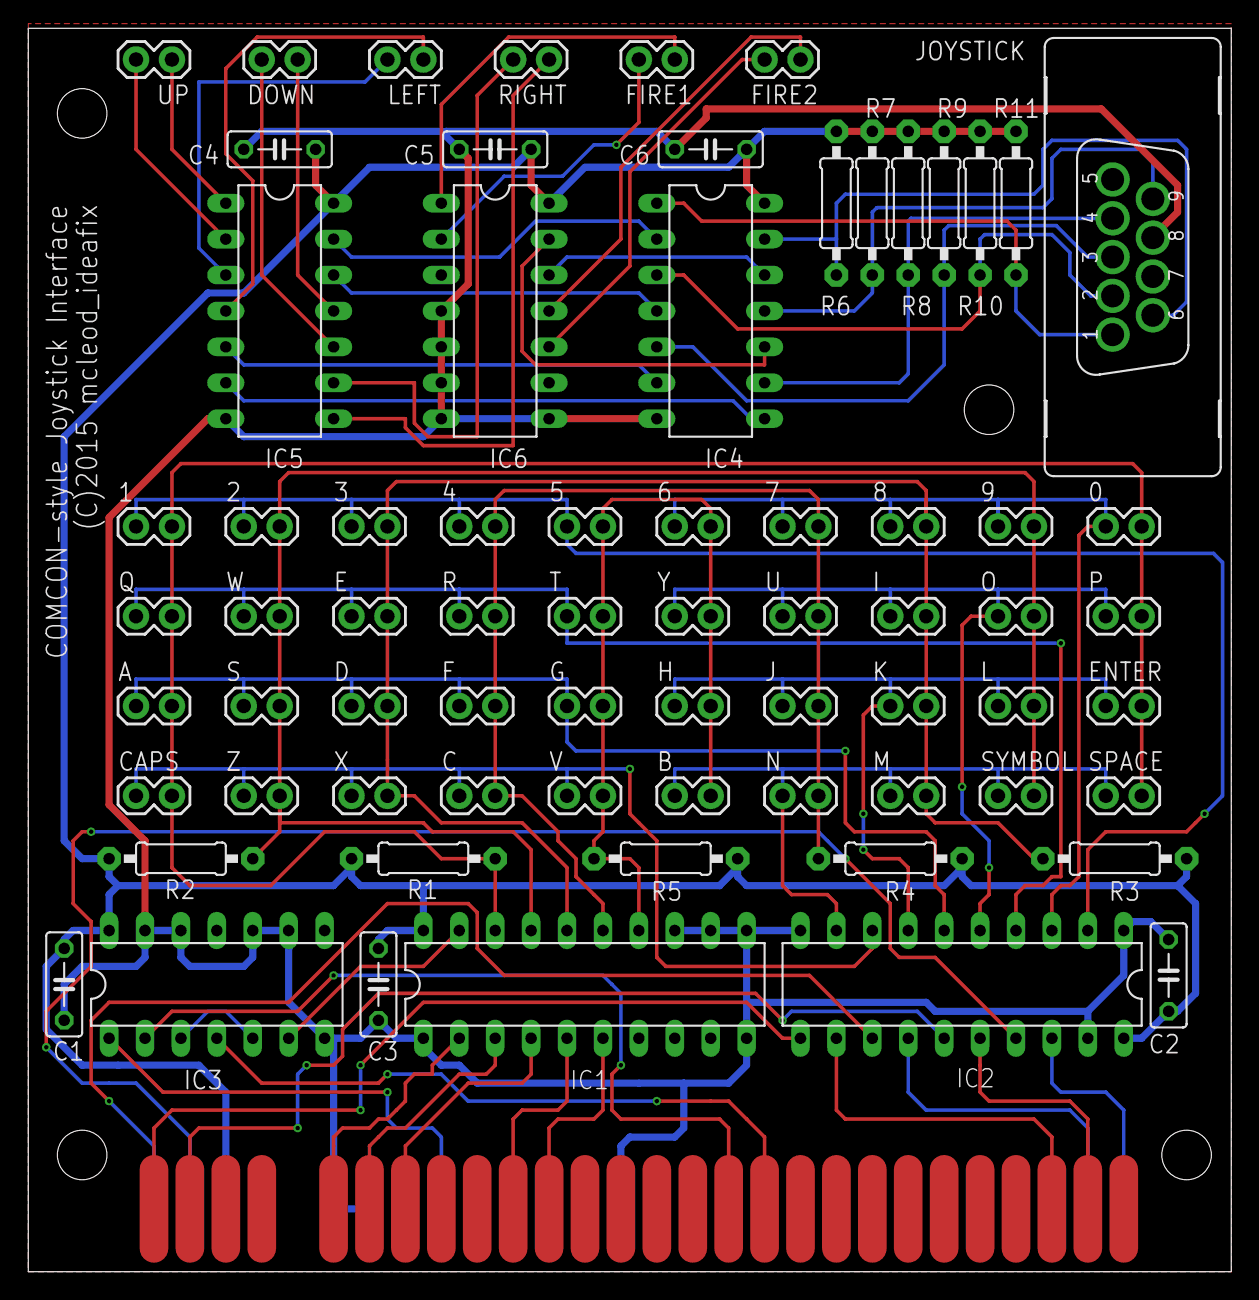
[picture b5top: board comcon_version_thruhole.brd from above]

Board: 2 copper layers, 85.1 x 87.9 mm, 71 parts (0 on the bottom side), 57 nets.

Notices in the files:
parts and their libraries:
SparkFun-Connectors: Licensing: Creative Commons ShareAlike 4.0 International - https://creativecommons.org/licenses/by-sa/4.0
